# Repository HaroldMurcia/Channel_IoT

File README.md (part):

# Channel_IoT

# **Índice**   
- 1 [INSTALACION DE HERRAMIENTAS](#id1)
  - 1.1 [MPLABX](#id2)
  - 1.2 [Instalación de **MPLAB X** en Ubuntu](#id3)
  - 1.3 [Instalación del compilador XC8 en ubuntu ](#id4)
  - 1.4 [Instalación de MPLAB CODE CONFIGURATOR MCC ](#id5)
  - 1.5 [LoRa Development Suite](#id6)
- 2 [HARDWARE](#id7)
  - 2.1 [Documentos relacionados ](#id8) 
  - 2.2 [Requerimientos de hardware](#id9)
  - 2.3 [Enlaces de interés](#id10)
- 3 [Diseño de schematic y PCB en Eagle](#id11)
  - 3.1 [Estructura de la PCB](#id12)
  - 3.2 [PCB  Botton y Top](#id13)
  - 3.3 [Modelo PCB en 3D](#id14)
- 4 [Errores de diseño](#id36)
- 5 [Comandos modulo RN2903](#id15)
   - 5.1 [Comandos radio ](#id16)
     - 5.1.1 [Comandos para inicializar el radio **modulación LoRa**](#id17)
     - 5.1.2 [Comandos de transmisión](#id18)
     - 5.1.3 [Comandos de recepción](#id19) 
- 6 [Protocolo serial ](#id21)
  - 6.1 [Tablas de contenido del mensaje](#id22)
    - 5.1.1 [Cabecera del mensaje](#id23)
    - 5.1.2 [Tabla de familia](#id24)
    - 5.1.2 [Descripción tablas](#id25)
- 7 [Documentación de código](#id26)
-  6.1 [Versiones de software](#id27)
    - 7.1.1 [Programación en PIC18Lf45k50](#id28)
    - 7.1.2 [Programación en dsPIC30F4011](#id29)
    - 7.1.2 [Interfaz nodo maestro](#id30)
- 8 [Resultados](#id31)
  - 8.1 [Apertura de compuerta](#id32)
  - 8.2 [Distancia del sensor de ultrasonido](#id33)
  - 8.3 [Alimentación de la board](#id34)
  - 8.4 [Temperatura de la board](#id35)

# INSTALACION DE HERRAMIENTAS  
## MPLABX  
Este algoritmo se ha realizado en [Mplab x IDE](https://www.microchip.com/en-us/development-tools-tools-and-software/mplab-x-ide) Versión 5.50 en el compilador [XC8]( https://www.microchip.com/en-us/development-tools-tools-and-software/mplab-xc-compilers) versión 2.32. A su vez se usó el plugin MCC [MPLAB® Code Configurator]( https://www.microchip.com/en-us/development-tools-tools-and-software/embedded-software-center/mplab-code-configurator) el cual esta disponible para windows linux y mac, este ayuda a generar las librerías básicas del micro controlador, cabe aclarar que la familia dspic30 no tiene soporte en este plugin.

## Instalación de **MPLAB X** en Ubuntu  
Primero se verifica la arquitectura de sistema, para ello abrimos una terminal y ejecutamos el siguiente comando:
```
uname - m
```

Se mira si la distribución de Linux tiene soporté de multi arquitectura en el caso de no tenerlo se debe instalar una librería especial
```
dpkg --print-foreign-architectures
```

Entonces aquí se observa que nos devuelve i386 lo que quiere decir que, si es multi arquitectura, ahora antes de seguir con el proceso se debe verificar que no haya actualizaciones del sistema 
```
sudo apt-get update
```
Ahora lo que se debe hacer es instalar las librerías para que **MPLAB**  sea compatible con instrucciones de procesador de 32bits
```
sudo apt-get install libc6:i386 libx11-6:i386 libxext6:i386 libstdc++6:i386 libexpat1:i386
```

Ahora se busca la  página oficial de microchip para descargar [MPLAB X IDE]( https://www.microchip.com/en-us/development-tools-tools-and-software/mplab-x-ide) en la sección de **Downloads, Documentation and Other Resources**
Después de haber descargado el software, nos dirigimos a la carpeta en la que se descargo
```
cd descargas/
```
Para la instalación del software, se descomprime el archivo y se convierte el archivo descargado a ejecutable  
```
tar -xvf MPLABX-v5.50-linux-installer.tar
chmod u+x MPLABX-v5.50-linux-installer.sh
```

Ejecutar el instalador 
```
sudo ./MPLABX-v5.50-linux-installer.sh
```

A continuación, se muestra las partes mas importantes del instalador 

Al final de la instalación se debe reiniciar el PC para completar el proceso de instalación 

## Instalación del compilador XC8 en ubuntu  
Ahora es necesario instalar el compilador para el microcontrolador que desee trabajar 8bits,16bits y 32bits [MPLAB XC]( https://www.microchip.com/en-us/development-tools-tools-and-software/mplab-xc-compilers) sección **Downloads, Documentation and Other Resources** y **compiler dowloads**

Después de haber descargado la aplicación, vamos a la carpeta en la que lo guardamos y lo volvemos un ejecutable y lo ejecutamos 
```
chmod u+x xc8-v2.32-full-install-linux-x64-installer.run
sudo ./xc8-v2.32-full-install-linux-x64-installer.run
```

Se deja todo por defecto y next

Al final de la instalación se debe reiniciar el PC para completar el proceso de instalación

## Instalación de MPLAB CODE CONFIGURATOR MCC  
Cabe aclarar que MCC es solamente compatible con la ultima versión de MPLAB X y esta disponible para todos los sistemas operativos. Además el procesos se realizo en ubuntu, sin embargo es el mismo proceso para Windows y MAC os.

MCC es un plugin que permite configurar algunos microcontroladores de una manera rápida y sencilla, ya que este genera una interfaz en la que se puede configurar una serie de parámetros, utilizar algunas librerías y este genera código de la librería según los parámetros estipulados  para comenzar a trabajar en el proyecto.

**Nota: MCC no es compatible con la familia DSPIC30**

* Abrir la aplicación de MPLAB X IDE
* Tools
* plugins
* Available Plugins
* Y buscamos MPLAB Code Configurator 
* Pulsar en install

Al final de la instalación se escoge reset now, y se reinicia MPLAB X después aparecerá de la siguiente manera, “si no se ha creado ningún proyecto”

## LoRa Development Suite  

Es una interfaz grafica que permite la configuración de los diferentes comandos que implementa modulo RN2903 y RN2483, de esta manera el usuario aprenda como debe enviar los datos de manera serial sin muchas complicaciones, **cabe aclarar que esta interfaz no es estrictamente necesaria para configurar el módulo RN2903,ya que es una guía, de igual forma, los comandos se pueden enviar mediarte el UART programndo el  microcontrolador** para más información  mirar la guía de comandos del [módulo RN2903]( https://ww1.microchip.com/downloads/en/DeviceDoc/RN2903%20LoRa%20Technology%20Module%20Command%20Reference%20User%20Guide-40001811B.pdf)

### instalación
Esta aplicación esta disponible para todos los sistemas operativos y se puede encontrar en la [pagina oficial de microchip]( https://www.microchip.com/wwwproducts/en/RN2903), en el apartado de **Documents**, **software libreires/firmware** se encuentran las aplicaciones, solo basta con abrir la aplicación darle next y **mirar la ruta de la carpeta en la que se va instalar ya que se debe ir a buscar la ampliación a ese  directorio** esto es para el caso de Windows. Ir al siguiente enlace en caso de [Linux
]( https://www.gaggl.com/2018/04/microchip-lorawan-development-utility-on-ubuntu/)

### RN2903 ACTUALIZAR FIREWARE
El siguiente video tiene como objetivo explicar la forma de actualizar el firmware del modulo RN2903 de la tarjeta LoRa Mote, dado el caso de que se allá borrado el firmware del módulo RN2903 [Video en youtube](https://youtu.be/kyjtmIkalMk)

# HARDWARE  
Este repositorio tiene como objetivo mostrar  los elementos que componen el sistema y su configuración en con construcción de esta, es decir la asignación de pines o conexiones de los dispositivos entre si.

## Documentos relacionados  
* [Configuración o asignación de pines](https://docs.google.com/spreadsheets/d/19cve4B_YzyOGqIv9DEK3eCqArvopMfsAZXm61Hay0jQ/edit?usp=sharing)

* [Google Drive](https://drive.google.com/drive/folders/19VFRMTp_xo8fuAuP7UYOIrlyNO1dNOWd?usp=sharing)
* [Diagrama de bloques](https://drive.google.com/file/d/1_osPgyQmuKj5nIkt5gdU3hPU3BZLeOLT/view?usp=sharing)
* [Schematic](https://github.com/HaroldMurcia/Channel_IoT/blob/master/Eagle/schematic.pdf)

## Requerimientos de hardware  
A continuación se muestran los componentes principales que encabezan el sistema, los demás dispositivos se encuentran en [Datasheet]( https://github.com/HaroldMurcia/Channel_IoT/tree/master/Hardware/Datasheet)
* [MaxSonar](https://co.mouser.com/ProductDetail/DFRobot/SEN0272?qs=T8HDo%252BTk69VWj8BEbH%252BU3Q%3D%3D)
* [LoRa Mote](https://www.microchip.com/Developmenttools/ProductDetails/dm164139)
* [Microchip RN2903](https://www.microchip.com/wwwproducts/en/RN2903)
* [Dspic30f4011](https://www.microchip.com/wwwproducts/en/dsPIC30F4011)

## Enlaces de interés  
* [Platformio](https://platformio.org/)
* [RAdioHead](https://www.airspayce.com/mikem/arduino/RadioHead/)

# Diseño de schematic y PCB en Eagle  
[Cotización de los componentes](https://docs.google.com/spreadsheets/d/1AnpxCE8uhZ4Mzhw6TfTGnhGRriO4N8LUufEemXK9A1I/edit#gid=807096094) En este link se entra la cotización de los diferentes componentes usados en la PCB exceptuando la tarjeta LoRa mote, Dspic, Tblocks y buzzer, dicha cotización se realizo para armar 3 tarjetas, mas adelante se describe  de manera superficial la función del componente.

## Estructura de la  PCB  
En el siguiente [enlace](https://docs.google.com/spreadsheets/d/1AnpxCE8uhZ4Mzhw6TfTGnhGRriO4N8LUufEemXK9A1I/edit#gid=1786186541) se encontrarán la distribución de los pines del DSpic para realizar las diferentes conexiones, este archivo contiene el número del pin, así como el label del esquemático de Eagle su tipo de puerto, es decir si es ADC, Digital etc.

La siguiente imagen muestra la distribución de cada uno de los componentes usados para la Pcb, estos componentes tienen su letra y numero correspondiente o identificador del componente, además de su valor si este lo requiere, cada  uno de los componentes se situó de manera estratégica, de tal manera que sea fácil soldar y acceder a este; de igual forma cada elemento esta lo más cerca posible a la conexión con otros dispositivos con los que se interconecta con el fin de tener la menor resistencia posible en la pista que los interconecta. 
La siguiente [tabla](https://docs.google.com/spreadsheets/d/1AnpxCE8uhZ4Mzhw6TfTGnhGRriO4N8LUufEemXK9A1I/edit#gid=1117524344) muestra la descripción mas detallada de cada elemento de la PCB.

Como se puede evidenciar la pcb diseñada es doble capa y cuenta con dos tamaños de anchura, cada uno de estos tamaños fueron calculados por medio de la norma IPS2221, estos cálculos se hicieron por medio de una calculadora que ofrece [Digikey]( https://www.digikey.com/es/resources/conversion-calculators/conversion-calculator-pcb-trace-width) para ello se busco en el datasheet de cada unos de los componentes las corrientes nominales, el consumo de cada uno de los componentes es bajo y en ancho de la pista es muy pequeño, por tanto por requerimientos mínimos que exigen algunas empresas para la fabricación de las pcb para  cada pista debe ser de 0.2mm, para este diseño se tomo un valor por arriba que es de 0.254mm, por otra parte para el calculo de las pistas de potencia se sumo la corriente nominal de todos los componentes, esto se hizo buscado el peor de los casos, lo cual hace suponer que todos los componentes están encendidos en el mismo momento. La corriente total fue alrededor de 1.3A, por tanto el anchor de la pista es de 0.55mm, sin embargo se sobre dimensiono un poco ya que algunos dispositivos pueden tener picos de corriente que muchas veces  no se especifica en el datasheet por tanto el ancho es de 1.016mm, por ultimo para realizar el cálculo se escogió una temperatura ambiente de 25°C y el aumento de temperatura de 30°C el espesor de 1oz/ft^2. 
[Tabla de cosumo y calculos de ruteo](https://docs.google.com/spreadsheets/d/1AnpxCE8uhZ4Mzhw6TfTGnhGRriO4N8LUufEemXK9A1I/edit#gid=618312286)

## PCB  Caras Botton Y Top  

## Modelo PCB en 3D 
La Pcb cuenta con diferentes componentes, la alimentación cuenta con un conector molex de 4 pines, el cual tiene una sola forma de conectar, por otra parte los indicadores visuales y audibles son indicadores del estado en que se encuentran el sistema, por otra parte el microcontrolador es que se encargara de procesar los diferentes sensores, procesamiento de datos y envió de datos al LoRa, por otra parte los sensores se leen mediante ADC, el bloque de comunicación de sistema de potencia se usa para comunicar un sistema de potencia que se encarga de abrir o cerrar la compuerta, los botones de calibración sirven para abrir o cerrar la compuerta calibrar la altura de sensores sonar, por último se dejó un puerto para programar el microcontrolador con un pickit mediante ICSP.

[Modelo en fusion360](https://a360.co/3zkWzcB)
Clave: 159753

# Errores de diseño 
- El primer error se encuentra en la parte de los pulsadores, las pistas para soldar cada pulsador son muy cortas, por tanto se deben dejar con mayor longitud a la actual, con el fin de que el pulsador se pueda soldar con mayor facilidad.
- cuando se construyeron las librerías del ADC, en la hoja de datos de la familia dsPIC30f se especifica que se deben conectar los pines 40 y 39 a la alimentación para la referencia del ADC, no obstante, la hoja de datos del dsPIC30f4011 especificaba que los pines eran usados para colocar un voltaje entre 2.7 y 5V, con lo anterior, se colocaron dos cables entre la base del dsPIC y el MCU, para poder leer las señales análogicas provenientes de los sensores.

# Comandos modulo RN2903

El modulo RN2903 tiene una gran cantidad de comandos, sin embargo solo se deben usar una cabecera para la comunicación ya sea **mac o radio**, en esta sección se implementaron los comandos radio, estos facilitan la comunicación entre dos módulos RN2903.

Por otra parte, los comandos en general se deben enviar con la misma cantidad de espacios que especifica la hoja de datos, a su vez al final de cada comando se de enviar retorno de carro **CR** y salto de línea **LF** .

## Comandos radio

### Comandos para inicializar el radio **modulación LoRa**

1. El siguiente comando permite cambiar el método de modulación utilizado por el módulo.
Además, la modificación del modo de funcionamiento no afecta los parámetros, variables o
registros previamente configurados. Así mismo, el comando es muy simple ya que solamente
decide si es LoRa o FSK. En este documento se trabaja los comandos relacionados con LoRa.
```http
  radio set mod <mode>
```
| Parametro   | Comando  | Parametro     |Description parametro              | Tipo de respuesta    |
| :--------   | :------- | :------------ |:--------------------------------- | :--------------------|
| `radio set` |  `mod`   | `<mode>`      |**String**. lora o fsk             |  ok o invalid_param  |

`Ejemplo` 
```http
  radio set mod lora\r\n
```
2. El siguiente comando determina la potencia de salida del transceptor. La cual se puede
ajustar por encima del límite especificado, este ajuste de potencia permite compensar algunas
pérdidas en el cable o línea de transmisión en dBm. El valor máximo que puede alcanzar es
de 17 dBm a 20 dBm
```http
  radio set pwr <pwrOut>
```
| Parametro   | Comando  |   Parametro   |Description parametro              | Tipo de respuesta    |
| :--------   | :------- | :------------ |:--------------------------------- | :--------------------|
| `radio set` |  `pwr`   |   `<pwrOut>`  |**Decimal**. de 2 hasta 20         |  ok o invalid_param  |

`Ejemplo` 
```http
   radio set pwr 3\r\n 
```
3. Este comando establece el ancho de banda de radio para el funcionamiento de LoRa,
ambos dispositivos deben tener el mismo ancho de banda, puesto que, ambos dispositivos se
comportan como transmisor y receptor 
```http
  radio set bw <bandWidth>
```
| Parametro   | Comando  |   Parametro   |Description parametro              | Tipo de respuesta    |
| :--------   | :------- | :------------ |:--------------------------------- | :--------------------|
| `radio set` |  `bw`   |   `<bandWidth>`  |**Decimal**. puede ser de 125,250,500 en KHz         |  ok o invalid_param  |

`Ejemplo` 
```http
   radio set bw 250\r\n 
```
4. El comando crc permite activar o desactivar la detección de errores, CRC Cyclic Redun-
dancy Check este comando se usa para detectar errores o cambios accidentales en datos
sin procesar. Por tanto, si el detector de errores encuentra irregularidades en los mensajes
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
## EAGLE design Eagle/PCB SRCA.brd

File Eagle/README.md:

# **Índice**   
- 3 [Diseño de schematic y PCB en Eagle](#id11)
  - 3.1 [ESTRUCTURA DEL PCB](#id12)
  - 3.2 [PCB TERMINADA CARAS BUTTOM Y TOP](#id13)
  - 3.3 [MODELO PCB EN 3D](#id14)

# Diseño de schematic y PCB en Eagle  
[Cotización de los componentes](https://docs.google.com/spreadsheets/d/1AnpxCE8uhZ4Mzhw6TfTGnhGRriO4N8LUufEemXK9A1I/edit#gid=807096094) En este link se entra la cotización de los diferentes componentes usados en la PCB exceptuando la tarjeta LoRa mote, Dspic, Tblocks y buzzer, dicha cotización se realizo para armar 3 tarjetas, mas adelante se describe  de manera superficial la función del componente.
## ESTRUCTURA DEL PCB  
En el siguiente [enlace](https://docs.google.com/spreadsheets/d/1AnpxCE8uhZ4Mzhw6TfTGnhGRriO4N8LUufEemXK9A1I/edit#gid=1786186541) se encontrarán la distribución de los pines del DSpic para realizar las diferentes conexiones, este archivo contiene el número del pin, así como el label del esquemático de Eagle su tipo de puerto, es decir si es ADC, Digital etc.

La siguiente imagen muestra la distribución de cada uno de los componentes usados para la Pcb, estos componentes tienen su letra y numero correspondiente o identificador del componente, además de su valor si este lo requiere, cada  uno de los componentes se situó de manera estratégica, de tal manera que sea fácil soldar y acceder a este; de igual forma cada elemento esta lo más cerca posible a la conexión con otros dispositivos con los que se interconecta con el fin de tener la menor resistencia posible en la pista que los interconecta. 
La siguiente [tabla](https://docs.google.com/spreadsheets/d/1AnpxCE8uhZ4Mzhw6TfTGnhGRriO4N8LUufEemXK9A1I/edit#gid=1117524344) muestra la descripción mas detallada de cada elemento de la Pcb.

Como se puede evidenciar la pcb diseñada es doble capa y cuenta con dos tamaños de anchura, cada uno de estos tamaños fueron calculados por medio de la norma IPS2221, estos cálculos se hicieron por medio de una calculadora que ofrece [Digikey]( https://www.digikey.com/es/resources/conversion-calculators/conversion-calculator-pcb-trace-width) para ello se busco en el datasheet de cada unos de los componentes las corrientes nominales, el consumo de cada uno de los componentes es bajo y en ancho de la pista es muy pequeño, por tanto por requerimientos mínimos que exigen algunas empresas para la fabricación de las pcb para  cada pista debe ser de 0.2mm, para este diseño se tomo un valor por arriba que es de 0.254mm, por otra parte para el calculo de las pistas de potencia se sumo la corriente nominal de todos los componentes, esto se hizo buscado el peor de los casos, lo cual hace suponer que todos los componentes están encendidos en el mismo momento. La corriente total fue alrededor de 1.3A, por tanto el anchor de la pista es de 0.55mm, sin embargo se sobre dimensiono un poco ya que algunos dispositivos pueden tener picos de corriente que muchas veces  no se especifica en el datasheet por tanto el ancho es de 1.016mm, por ultimo para realizar el cálculo se escogió una temperatura ambiente de 25°C y el aumento de temperatura de 30°C el espesor de 1oz/ft^2. 
[Tabla de cosumo y calculos de ruteo](https://docs.google.com/spreadsheets/d/1AnpxCE8uhZ4Mzhw6TfTGnhGRriO4N8LUufEemXK9A1I/edit#gid=618312286)

## PCB TERMINADA CARAS BUTTOM Y TOP  

## MODELO PCB EN 3D 
La Pcb cuenta con diferentes componentes, la alimentación cuenta con un conector molex de 4 pines, el cual tiene una sola forma de conectar, por otra parte los indicadores visuales y audibles son indicadores del estado en que se encuentran el sistema, por otra parte el microcontrolador es que se encargara de procesar los diferentes sensores, procesamiento de datos y envió de datos al LoRa, por otra parte los sensores se leen mediante ADC, el bloque de comunicación de sistema de potencia se usa para comunicar un sistema de potencia que se encarga de abrir o cerrar la compuerta, los botones de calibración sirven para abrir o cerrar la compuerta calibrar la altura de sensores sonar, por último se dejó un puerto para programar el microcontrolador con un pickit mediante ICSP.

[Modelo en fusion360](https://a360.co/3zkWzcB)
Clave: 159753

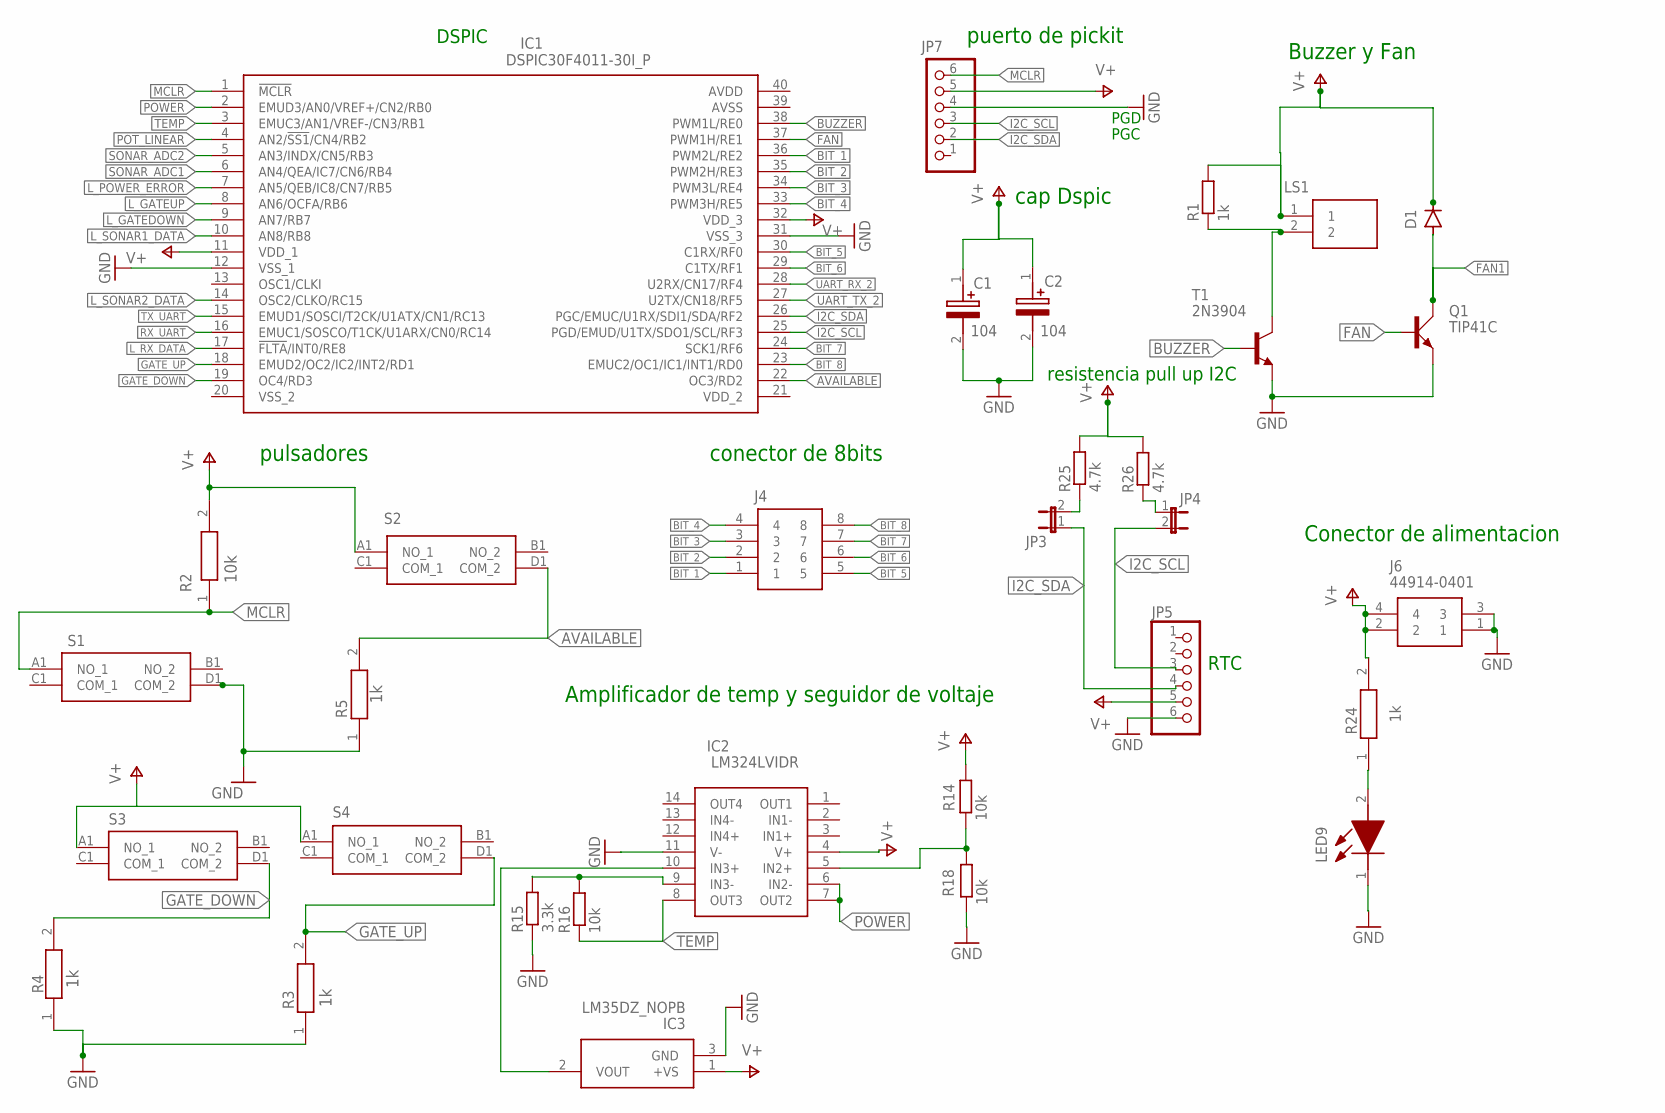
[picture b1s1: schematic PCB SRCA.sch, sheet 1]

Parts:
C1, C2: TAJR104K020RNJ; CAPPM2014X120N
D1: 1N4148DO35-7; DO35-7
IC1: DSPIC30F4011-30I_P; DIP1543W58P254L5175H635Q40N
IC2: LM324LVIDR; SOIC127P600X175-14N
IC3: LM35DZ_NOPB; LP0003A
J4: 44914-0801
J6: 44914-0401
JP3, JP4: JP1E; JP1
JP5, JP7: PINHD-1X6; 1X06
LED9: 599-0181-007F; LEDC2012X70N
LS1: PS1240P02BT
Q1: TIP41C; TO220AV
R1: 1k; 0207/10
R2, R3, R4, R5, R24: RC0805FR-071KL; RESC2012X60N
R14, R16, R18: 10k; 0207/10
R15: 3.3k; 0207/10
R25, R26: 4.7k; 0207/10
S1, S2, S3, S4: PTS645SK50JSMTR92_LFS; PTS645SK50JSMTR92LFS
T1: 2N3904; TO92

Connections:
AVAILABLE: IC1.22 (OC3/RD2), R5.2, S2.D1 (COM_2)
BIT_1: IC1.36 (PWM2L/RE2), J4.1
BIT_2: IC1.35 (PWM2H/RE3), J4.2
BIT_3: IC1.34 (PWM3L/RE4), J4.3
BIT_4: IC1.33 (PWM3H/RE5), J4.4
BIT_5: IC1.30 (C1RX/RF0), J4.5
BIT_6: IC1.29 (C1TX/RF1), J4.6
BIT_7: IC1.24 (SCK1/RF6), J4.7
BIT_8: IC1.23 (EMUC2/OC1/IC1/INT1/RD0), J4.8
BUZZER: IC1.38 (PWM1L/RE0), T1.2 (B)
FAN: IC1.37 (PWM1H/RE1), Q1.B
FAN1: D1.A, Q1.C; also elsewhere on the board
GATE_DOWN: IC1.19 (OC4/RD3), R4.2, S3.D1 (COM_2)
GATE_UP: IC1.18 (EMUD2/OC2/IC2/INT2/RD1), R3.2, S4.D1 (COM_2)
GND: C1.2 (-), C2.2 (-), IC1.12 (VSS_1), IC1.31 (VSS_3), IC2.11 (V-), IC3.3 (GND), J6.1, J6.3, JP5.6, JP7.4, LED9.1 (K), Q1.E, R3.1, R4.1, R5.1, R15.1, R18.1, S1.D1 (COM_2), T1.3 (E); also elsewhere on the board
I2C_SCL: IC1.25 (PGD/EMUD/U1TX/SDO1/SCL/RF3), JP4.2, JP5.3, JP7.3; also elsewhere on the board
I2C_SDA: IC1.26 (PGC/EMUC/U1RX/SDI1/SDA/RF2), JP3.1, JP5.4, JP7.2; also elsewhere on the board
L_GATEDOWN: IC1.9 (AN7/RB7); also elsewhere on the board
L_GATEUP: IC1.8 (AN6/OCFA/RB6); also elsewhere on the board
L_POWER_ERROR: IC1.7 (AN5/QEB/IC8/CN7/RB5); also elsewhere on the board
L_RX_DATA: IC1.17 (!FLTA!/INT0/RE8); also elsewhere on the board
L_SONAR1_DATA: IC1.10 (AN8/RB8); also elsewhere on the board
L_SONAR2_DATA: IC1.14 (OSC2/CLKO/RC15); also elsewhere on the board
MCLR: IC1.1 (!MCLR), JP7.6, R2.1, S1.A1 (NO_1)
unnamed: IC2.9 (IN3-), R15.2, R16.2
unnamed: IC2.10 (IN3+), IC3.2 (VOUT)
unnamed: JP3.2, R25.1
unnamed: LS1.2, R1.1, T1.1 (C)
unnamed: LED9.2 (A), R24.1
unnamed: JP4.1, R26.1
unnamed: IC2.5 (IN2+), R14.1, R18.2
POT_LINEAR: IC1.4 (AN2/!SS1!/CN4/RB2); also elsewhere on the board
POWER: IC1.2 (EMUD3/AN0/VREF+/CN2/RB0), IC2.6 (IN2-), IC2.7 (OUT2)
RX_UART: IC1.16 (EMUC1/SOSCO/T1CK/U1ARX/CN0/RC14); also elsewhere on the board
SONAR_ADC1: IC1.6 (AN4/QEA/IC7/CN6/RB4); also elsewhere on the board
SONAR_ADC2: IC1.5 (AN3/INDX/CN5/RB3); also elsewhere on the board
TEMP: IC1.3 (EMUC3/AN1/VREF-/CN3/RB1), IC2.8 (OUT3), R16.1
TX_UART: IC1.15 (EMUD1/SOSCI/T2CK/U1ATX/CN1/RC13); also elsewhere on the board
UART_RX_2: IC1.28 (U2RX/CN17/RF4); also elsewhere on the board
UART_TX_2: IC1.27 (U2TX/CN18/RF5); also elsewhere on the board
V+: C1.1 (+), C2.1 (+), D1.C, IC1.11 (VDD_1), IC1.32 (VDD_3), IC2.4 (V+), IC3.1 (+VS), J6.2, J6.4, JP5.5, JP7.5, LS1.1, R1.2, R2.2, R14.2, R24.2, R25.2, R26.2, S2.A1 (NO_1), S3.A1 (NO_1), S4.A1 (NO_1); also elsewhere on the board

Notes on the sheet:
pulsadores
Amplificador de temp y seguidor de voltaje
conector de 8bits
cap Dspic
puerto de pickit
Conector de alimentacion
resistencia pull up I2C
RTC
DSPIC
10k
104
Buzzer y Fan
PGD
PGC

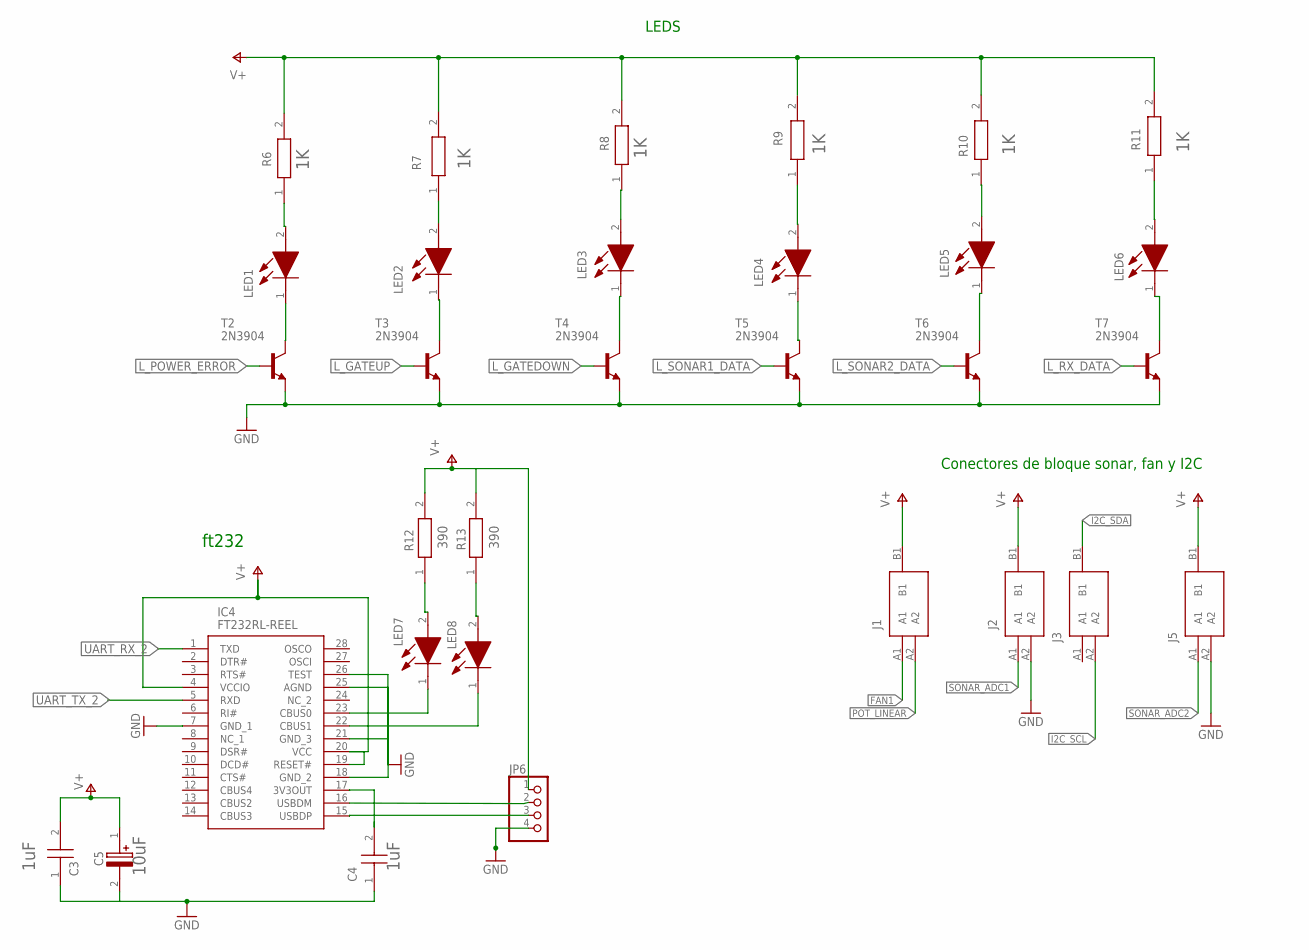
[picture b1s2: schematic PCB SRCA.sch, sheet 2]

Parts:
C3, C4: C0805X104K1RAC3316; CAPC2012X100N
C5: UUP1C100MCL1GS; CAPAE530X610N
IC4: FT232RL-REEL; SOP65P778X200-28N
J1, J2, J3, J5: TBL002A-350-03GR-2OR; TBL002A35003GR2OR
JP6: PINHD-1X4; 1X04
LED1, LED2, LED3, LED4, LED5, LED6, LED7, LED8: 599-0181-007F; LEDC2012X70N
R6, R7, R8, R9, R10, R11, R12, R13: RC0805FR-071KL; RESC2012X60N
T2, T3, T4, T5, T6, T7: 2N3904; TO92

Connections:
FAN1: J1.A1; also elsewhere on the board
GND: C3.1, C4.1, C5.2 (-), IC4.7 (GND_1), IC4.18 (GND_2), IC4.21 (GND_3), IC4.25 (AGND), IC4.26 (TEST), J2.A2, J5.A2, JP6.4, T2.3 (E), T3.3 (E), T4.3 (E), T5.3 (E), T6.3 (E), T7.3 (E); also elsewhere on the board
I2C_SCL: J3.A2; also elsewhere on the board
I2C_SDA: J3.B1; also elsewhere on the board
L_GATEDOWN: T4.2 (B); also elsewhere on the board
L_GATEUP: T3.2 (B); also elsewhere on the board
L_POWER_ERROR: T2.2 (B); also elsewhere on the board
L_RX_DATA: T7.2 (B); also elsewhere on the board
L_SONAR1_DATA: T5.2 (B); also elsewhere on the board
L_SONAR2_DATA: T6.2 (B); also elsewhere on the board
unnamed: LED1.2 (A), R6.1
unnamed: IC4.23 (CBUS0), LED7.1 (K)
unnamed: LED1.1 (K), T2.1 (C)
unnamed: LED2.2 (A), R7.1
unnamed: LED2.1 (K), T3.1 (C)
unnamed: LED3.1 (K), T4.1 (C)
unnamed: LED4.2 (A), R9.1
unnamed: LED5.2 (A), R10.1
unnamed: LED3.2 (A), R8.1
unnamed: LED4.1 (K), T5.1 (C)
unnamed: LED6.2 (A), R11.1
unnamed: LED7.2 (A), R12.1
unnamed: LED8.2 (A), R13.1
unnamed: LED5.1 (K), T6.1 (C)
unnamed: LED6.1 (K), T7.1 (C)
unnamed: IC4.22 (CBUS1), LED8.1 (K)
unnamed: C4.2, IC4.17 (3V3OUT)
unnamed: IC4.16 (USBDM), JP6.2
unnamed: IC4.15 (USBDP), JP6.3
POT_LINEAR: J1.A2; also elsewhere on the board
SONAR_ADC1: J2.A1; also elsewhere on the board
SONAR_ADC2: J5.A1; also elsewhere on the board
UART_RX_2: IC4.1 (TXD); also elsewhere on the board
UART_TX_2: IC4.5 (RXD); also elsewhere on the board
V+: C3.2, C5.1 (+), IC4.4 (VCCIO), IC4.19 (RESET#), IC4.20 (VCC), J1.B1, J2.B1, J5.B1, JP6.1, R6.2, R7.2, R8.2, R9.2, R10.2, R11.2, R12.2, R13.2; also elsewhere on the board

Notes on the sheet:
Conectores de bloque sonar, fan y I2C
LEDS
390
ft232
1uF
10uF

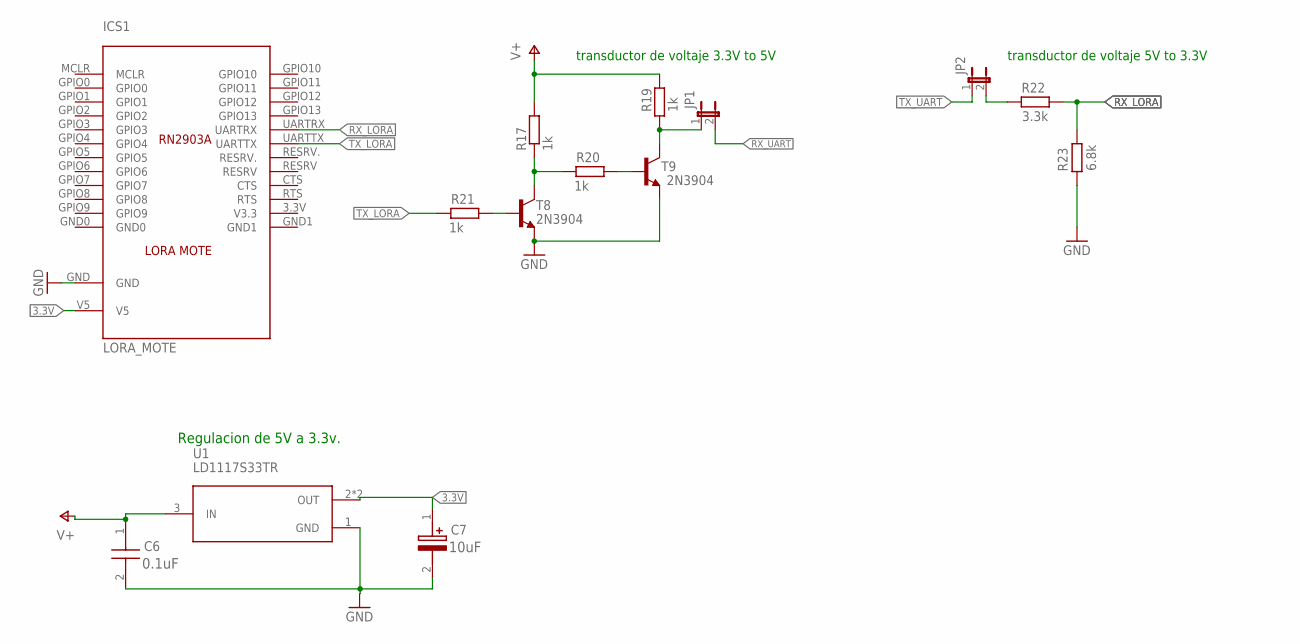
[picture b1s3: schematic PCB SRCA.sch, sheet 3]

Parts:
C6: C0805X104K1RAC3316; CAPC2012X100N
C7: UUP1C100MCL1GS; CAPAE530X610N
ICS1: LORA_MOTE; LORA_MOTE_RN2903
JP1, JP2: JP1E; JP1
R17, R19, R20, R21: 1k; 0207/10
R22: 3.3k; 0207/10
R23: 6.8k; 0207/10
T8, T9: 2N3904; TO92
U1: LD1117S33TR; SOT230P700X180-4N

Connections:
3.3V: C7.1 (+), ICS1.V5, U1.2 (OUT), U1.4 (OUT)
GND: C6.2, C7.2 (-), ICS1.GND, R23.2, T8.3 (E), T9.3 (E), U1.1 (GND); also elsewhere on the board
unnamed: R17.1, R20.2, T8.1 (C)
unnamed: R21.1, T8.2 (B)
unnamed: R20.1, T9.2 (B)
unnamed: JP2.2, R22.2
unnamed: JP1.1, R19.1, T9.1 (C)
RX_LORA: ICS1.UARTRX, R22.1, R23.1
RX_UART: JP1.2; also elsewhere on the board
TX_LORA: ICS1.UARTTX, R21.2
TX_UART: JP2.1; also elsewhere on the board
V+: C6.1, R17.2, R19.2, U1.3 (IN); also elsewhere on the board

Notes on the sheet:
transductor de voltaje 3.3V to 5V
transductor de voltaje 5V to 3.3V
Regulacion de 5V a 3.3v.
0.1uF
10uF

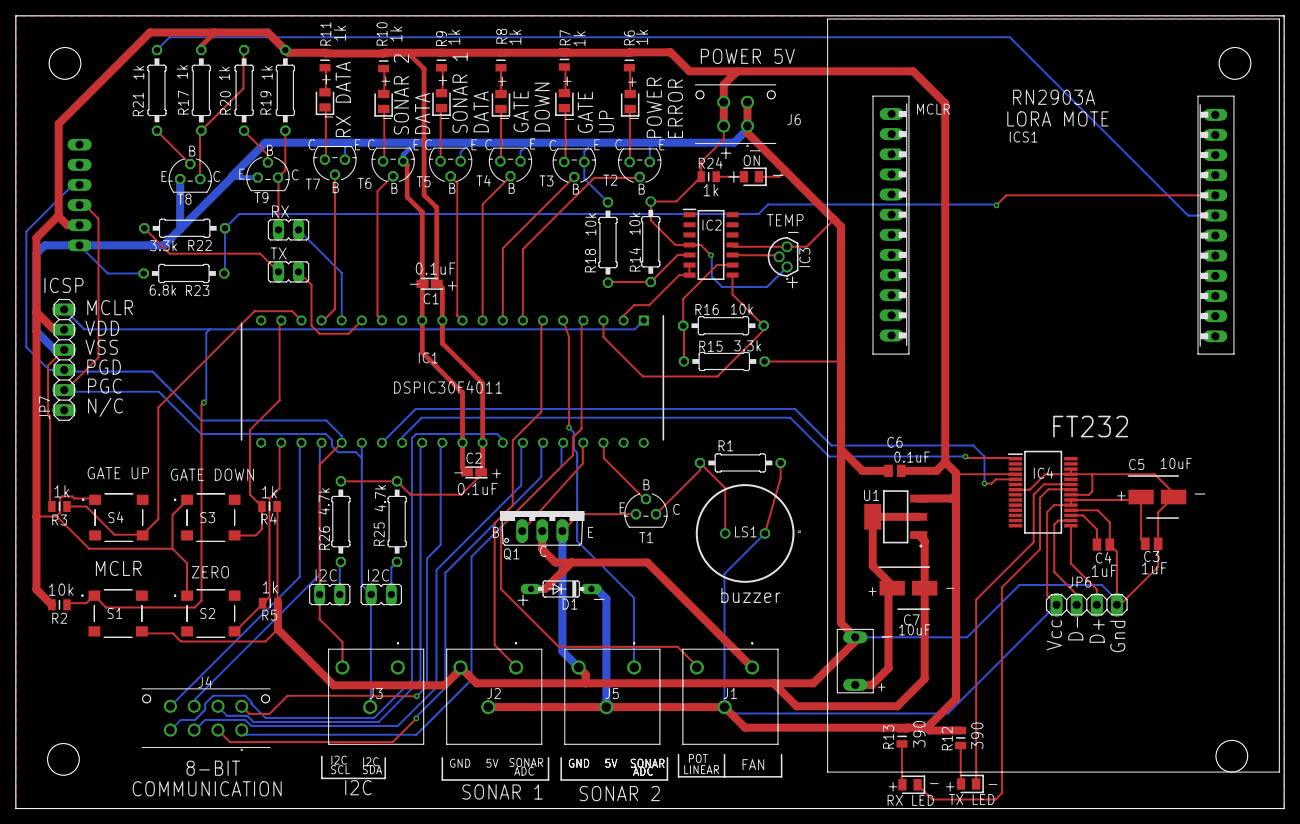
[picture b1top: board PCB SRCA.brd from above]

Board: 2 copper layers, 160.0 x 100.0 mm, 77 parts (1 on the bottom side), 68 nets.

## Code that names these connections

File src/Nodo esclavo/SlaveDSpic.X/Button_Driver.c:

/*
 * File  : Button_Driver.c
 * Author: Johan Avila 
 * Mail  : ingenieroavila21@gmail.com
 */

#include <xc.h>
#include "Button_Driver.h"

void Init_Button_Driver(void) {

    // init output Volts 0 
    LATDbits.LATD1 = 0;
    LATDbits.LATD2 = 0;
    LATDbits.LATD3 = 0;

    // determines id it is input(1) or output(0)
    TRISDbits.TRISD1 = 1; // RD1 Gate_Up
    TRISDbits.TRISD2 = 1; // RD2 Zero
    TRISDbits.TRISD3 = 1; // RD3 Gate_Down
}

// functions
// returns the value of the pin (1: 5 volts; 0: 0 volts)

int Button_Gate_Up(void) {
    return (PORTDbits.RD1);
}

int Button_Zero(void) {
    return (PORTDbits.RD2);
}

int Button_Gate_Down(void) {
    return (PORTDbits.RD3);
}

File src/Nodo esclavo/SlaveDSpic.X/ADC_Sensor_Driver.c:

/*
 * File:   Channel_Gate.c
 * Position : Estudiante de Paz y Region 
 * Author: Johan Avila 
 * Mail  : ingenieroavila21@gmail.com
 * Reviewer and approver  : Oscar Daniel Rodriguez Gallego
 * Change : Oscar Daniel Rodrguez Gallego
 */

#include <xc.h>

#include "ADC_Sensor_Driver.h"
#include "LoRa_RN2903A.h"

const float Resolution_ADC = (5.0) / (1024); // (AVDD / 2^10bit) 
// ok
float Volts_Power_ADC = 0.0; // RB0
float Volts_Temp_ADC = 0.0; // RB1
float Volts_Gate_ADC = 0.0; // RB2
float Volts_Sonar_2_ADC = 0.0; // RB3
float Volts_Sonar_1_ADC = 0.0; // RB4
float Voltaje_max=0.0,Voltaje_min=0.0;

void Init_ADC_Sensors_Driver(void) {
    // ADPCFG configuration ok
    TRISBbits.TRISB0 = 1;
    TRISBbits.TRISB1 = 1;
    TRISBbits.TRISB2 = 1;
    TRISBbits.TRISB3 = 1;
    TRISBbits.TRISB4 = 1;
    // digital ports 1 ; analog ports 0; ports B
    ADPCFGbits.PCFG0 = 0; // RB0 intput analog ports
    ADPCFGbits.PCFG1 = 0; // RB1 intput analog ports
    ADPCFGbits.PCFG2 = 0; // RB2 intput analog ports  
    ADPCFGbits.PCFG3 = 0; // RB3 intput analog ports
    ADPCFGbits.PCFG4 = 0; // RB4 intput analog ports
        // ADCON1 configuration ok
    ADCON1bits.ADSIDL = 0; // Continue module operation in Idle mode
    ADCON1bits.FORM = 0b00; // Data Output Format bits Integer
    ADCON1bits.SSRC = 0b000; // Clearing SAMP bit ends sampling and starts conversion
    ADCON1bits.SIMSAM = 0; // Samples multiple channels individually in sequence
    ADCON1bits.ASAM = 0; // A/D Sample Auto-Start bit,Sampling begins when SAMP bit set 

    // ADCON2 configuration ok
    ADCON2bits.VCFG = 0b000; // Voltage Reference(AVDD - AVSS)
    ADCON2bits.CSCNA = 0; // Do not scan inputs
    ADCON2bits.CHPS = 0b11; // Selects Channels Utilized CH0, CH1, CH2 and CH3
    ADCON2bits.BUFS = 1; //  A/D is currently filling buffer 0x8-0xF, user should access data in 0x0-0x7
    ADCON2bits.SMPI = 0b1000; // Sample/Convert Sequences Per Interrupt Selection bits
    ADCON2bits.BUFM = 1; // Buffer configured as two 8-word buffers ADCBUF(15...8), ADCBUF(7...0)
    ADCON2bits.ALTS = 1; // Uses MUX A input multiplexer settings for first sample, then alternate between MUX B and MUX A input multiplexer settings for all subsequent samples

    // ADCHS configuration ok
    // MUX A Multiplexer Setting bits
    ADCHSbits.CH123NA = 0b00; // CH1, CH2, CH3 negative input is VREF -
    ADCHSbits.CH123SA = 0; // CH1:AN0, CH2:AN1, CH3:AN2
    ADCHSbits.CH0NA = 0; // Channel 0 negative input is VREF-
    ADCHSbits.CH0SA = 0b0011; // CH0:AN3

    // MUX B Multiplexer Setting bits
    ADCHSbits.CH123NB = 0b00; // CH1, CH2, CH3 negative input is VREF -
    ADCHSbits.CH123SB = 0; // CH1:AN0, CH2:AN1, CH3:AN2
    ADCHSbits.CH0NB = 0; // Channel 0 negative input is VREF-
    ADCHSbits.CH0SB = 0b0100; // CH0:AN4

    // ADCSSL configuration add daniel rodriguez gallego
    ADCSSLbits.CSSL0 = 0;
    ADCSSLbits.CSSL1 = 0;
    ADCSSLbits.CSSL2 = 0;
    ADCSSLbits.CSSL3 = 0;
    ADCSSLbits.CSSL4 = 0;

    // ADCON3 configuration ok
    ADCON3bits.SAMC = 18; // Sample Time bits
    ADCON3bits.ADRC = 1; // A/D internal RC clock
    // TAD = 333.33 nsec
    // FCY = FOSC/4 120Mhz : 30Mhz
    // ADCS = ( (2*TAD) / (1/FCY) ) - 1
    ADCON3bits.ADCS = 9; // Conversion Clock Select bits
    
    ADCON1bits.ADON = 1; //  Conversion Status bit on
}

void Sensor_Reading_ADC(void) {

    ADCON1bits.SAMP = 1; // Bit para habilitar muestreo
    __delay_ms(10);
    ADCON1bits.SAMP = 0; // Retiene el muestreo

    // MUX A Multiplexer
    Volts_Power_ADC = (ADCBUF1 * Resolution_ADC ); // RB0
    Volts_Temp_ADC = (ADCBUF2 * Resolution_ADC * 100) / 4; // RB1 4 corresponde a la ganancia de AOP
    Volts_Gate_ADC = (ADCBUF3 * Resolution_ADC); // RB2  
    Volts_Sonar_2_ADC = (ADCBUF0 * 5); // RB3

    // MUX B Multiplexer
    Volts_Sonar_1_ADC = (ADCBUF4 * 5); // RB4
}

float Get_Volts_Power_ADC(void) {
    return Volts_Power_ADC;
}

float Get_Volts_Temp_ADC(void) {

    return Volts_Temp_ADC;
}

float Get_Percentage_Gate_ADC(void) {
    /*
     * como se tiene una condicion de un voltaje minimo y un voltaje maximo 
     * el porcentajes es una regla de 3, en la que la lectura del adc se le resta el voltaje minimo ya que este 
     * es un offeset, al igual se hace Voltaje maximo, la idea es que el voltaje minimo represente al cero
     * y el maximo al 100%
     */
    float percentage = ((Volts_Gate_ADC-Voltaje_min)*100)/(Voltaje_max - Voltaje_min);
    if(percentage<=0){
        percentage = 0;
    }else if(percentage >= 100)
    {
        percentage =100;
    }else{
        percentage = percentage;//el valor que tiene
    }
    return percentage;
}

float Get_Volts_Sonar_1_ADC(void) {
//    Led_Sonar1(1);
//    __delay_ms(50);
//    Led_Sonar1(0);
    return Volts_Sonar_1_ADC;
}

float Get_Volts_Sonar_2_ADC(void) {
//    Led_Sonar2(1);
//    __delay_ms(50);
//    Led_Sonar2(0);
    return Volts_Sonar_2_ADC;
}

void Init_Percentage(float Vmax, float Vmin){
    Voltaje_max = Vmax;
    Voltaje_min = Vmin; 
}

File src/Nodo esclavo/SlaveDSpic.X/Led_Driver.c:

/*
 * File  : Led_Driver.c
 * Position : Estudiante de Paz y Region 
 * Author: Johan Avila 
 * Mail  : ingenieroavila21@gmail.com
 * Reviewer and approver  : Oscar Daniel Rodriguez Gallego
 * Change : Oscar Daniel Rodrguez Gallego
 */

#include <xc.h>
//#include <libpic30.h>
#include "Led_Driver.h"


// 1 : On ; 0 : Off
void Init_Led_Driver(void)
{
    // digital ports 1 ; analog ports 0; ports B
    ADPCFGbits.PCFG5 = 1; // Rb5
    ADPCFGbits.PCFG6 = 1; // Rb6
    ADPCFGbits.PCFG7 = 1; // Rb7
    ADPCFGbits.PCFG8 = 1; // Rb8 

    // determines id it is input(1) or output(0)
    TRISBbits.TRISB5 = 0; // Reb     Rb5 Power Error
    TRISBbits.TRISB6 = 0; // Yellow  Rb6 Gateup 
    TRISBbits.TRISB7 = 0; // White   Rb7 GateDown
    TRISBbits.TRISB8 = 0; // Yellow  Rb8 Sonar1
    TRISCbits.TRISC15 = 0; // White   C15 Sonar2
    TRISEbits.TRISE8 = 0; // Yellow  E8  Rx

    // init output Volts 0 
    LATBbits.LATB5 = 0;
    LATBbits.LATB6 = 0;
    LATBbits.LATB7 = 0;
    LATBbits.LATB8 = 0;
    LATCbits.LATC15 = 0;
    LATEbits.LATE8 = 0;
}

// functions
// 1 : On ; 0 : Off

void Led_Power_Error(int option_LedDri) {
    LATBbits.LATB5 = option_LedDri;
}

void Led_Gateup(int option_LedDri) {
    LATBbits.LATB6 = option_LedDri;
}

void Led_GateDown(int option_LedDri) {
    LATBbits.LATB7 = option_LedDri;
}

void Led_Sonar1(int option_LedDri) {
    LATBbits.LATB8 = option_LedDri;
}

void Led_Sonar2(int option_LedDri) {
    LATCbits.LATC15 = option_LedDri;
}

void Led_Rx(int option_LedDri) {
    LATEbits.LATE8 = option_LedDri;
}
/// oscar daniel Rodriguez 
void Turn_on_pic(void)
{
    int i;
    int size = 2;
    for (i = 0; i < size; i++) 
    {
        LATBbits.LATB5 = ~LATBbits.LATB5;
        __delay_ms(50);
        LATBbits.LATB5 = ~LATBbits.LATB5;
        __delay_ms(50);
        LATBbits.LATB6 = ~LATBbits.LATB6;
        __delay_ms(50);
        LATBbits.LATB6 = ~LATBbits.LATB6;
        __delay_ms(50);
        LATBbits.LATB7 = ~LATBbits.LATB7;
        __delay_ms(50);
        LATBbits.LATB7 = ~LATBbits.LATB7;
        __delay_ms(50);
        LATBbits.LATB8 = ~LATBbits.LATB8;
        __delay_ms(50);
        LATBbits.LATB8 = ~LATBbits.LATB8;
        __delay_ms(50);
        LATCbits.LATC15 = ~LATCbits.LATC15;
        __delay_ms(50);
        LATCbits.LATC15 = ~LATCbits.LATC15;
        __delay_ms(50);
        LATEbits.LATE8 = ~LATEbits.LATE8;
        __delay_ms(50);
        LATEbits.LATE8 = ~LATEbits.LATE8;
        __delay_ms(50);
    }
}
void Led_turn_on_all(void){
        Led_Power_Error(1);
    Led_Gateup(1);
    Led_GateDown(1);
    Led_Sonar1(1);
    Led_Sonar2(1);
    Led_Rx(1);
    __delay_ms(300);

    //        LATBbits.LATB5 = 0;
    Led_Power_Error(0);
    Led_Gateup(0);
    Led_GateDown(0);
    Led_Sonar1(0);
    Led_Sonar2(0);
    Led_Rx(0);
    __delay_ms(300);
}

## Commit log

2021-03-24 24.03.2021
2021-04-01 datashet
    se agregaron los datasheet de el sensor ultra sonido, la tarjeta LoRa el Dspic.
2021-04-01 Diseño de PCB
2021-04-01 datasheet
2021-04-10 Correccion readme
    se agregaron los links de google drive, los link de la pagina oficial en la cual se compraron los componentes aun falta por especificar
    mas cosas
2021-04-14 schematic
    este documento contiene el desarrollos esquemático del pcb
2021-04-14 Update Readme.md
    Se arreglo el diagrama de bloques
2021-04-14 eagle
    esquematico con los pootprint
2021-04-14 esquematico
2021-04-15 pres macro
2021-04-21 actulizacion tarjeta
    se realiz ajustes del esquematico
2021-04-21 organizacion
2021-05-16 pdf tarjeta
    este pdf contiene el esquematico de las conexiones realizadas hasta el momento
2021-05-16 Esquematico
    se actulizo el esquematico
2021-05-16 16/05/2021
    actualizacion
2021-05-28 New links
2021-06-28 28/06/2021
    se agrego la documentación del código fuente de la tarjeta LoRa Mote
2021-06-28 28/06/2021
    Codigo fuente
2021-06-28 27/06/2021
2021-06-29 29/06/2021
    actualización del firmware de una tarjeta loRa
2021-07-06 6/07/2021
2021-07-07 6/07/2021
    actualizacion de codigos de transmision y recepcion
2021-07-07 06/07/2021
    cambio de carpeta
2021-07-07 06/07/2021
    explicación de lorasuit y comandos
2021-07-07 06/07/2021
2021-07-07 07/07/2021
2021-07-07 07/07/2021
    Se agrego el proceso de instalación de los programas usados aun falta agregar la instalacion de lora suit
2021-07-08 07/07/2021
    Se termino de agregar los coma nos de radio
2021-07-08 Harold 08.07.21 Tx>>Rx
2021-07-15 14/07/2021
    actualizacIón de la PCB
2021-07-21 21/07/2021
    cambios en las posiciones de los componentes y pistas
2021-07-22 22/07/2021
2021-07-22 22/07/2021
    Se actualizo la pcb con todos los componentes y pistas, además se agregó las librerías del proyecto
2021-08-12 11/08/2021
    cambios pre finales del pcb y sus componentes
2021-08-13 12/08/2021
    correccion de sensor de temperatura
2021-08-13 12/08/2021
2021-08-21 20/08/2021
    se adjunta los archivos de la PCB final con logo y archivo gerber
2021-08-23 23-08-2021
    actualizaciones de nombres y logos
2021-08-24 23-08-2021
    pcb y cotización
2021-08-24 24-08-2021
    correccion de errores en pistas
2021-08-25 25-08-2021
    Cotizacion colcircuiotso
2021-08-26 25-08-2021
    ajustes
2021-08-26 26-08-2021
    Actulizacion de la pcb correccion de pistas separacion entre ellas
2021-09-01 31-08-2021
    se agregaron las librerías del proyecto se hizo algunas correciones en la parte de el sensor de temperatura y se hizo se coloco un regulador de 5V a 3.3V para la lora mote
2021-09-01 31-08-2021
    imagenes del pcb
2021-09-01 31-08-2021
    se cargo las nuevas imágenes al readme y el modelo 3d
2021-09-01 01-09-2021
    readme para basar se en la construccion del protocolo
2021-09-05 04-09-2021
    cambios de la nueva pcb se agrego cambios del uart entre dspic y lora
2021-09-06 06-09-2021
    se revirtio el cambio de el divisor de voltaje del lora al DSPIC
2021-09-06 06/09/2021
2021-09-06 06-09-2021
2021-09-21 21-09-2021
2021-09-21 21-08-2021
    se adiciono la explicación del protocolo serial, aun falta agregar las funciones, se esta revisando un fallo especifico
2021-09-23 23-09-2021
2021-11-18 18-11-2021
    Copia de codigo de comunicacion avanzada de LoRa Mote a LoRa Mote
    1. aqui se encuentra la libreria Lora basica
    2. protocolo de comunicacion
2022-01-28 27/01/2022
2022-01-28 27-01-2022
2022-03-15 14-03-2022
    gif
2022-03-15 14-03-2022
    se agregó los datashet del proyecto
2022-03-15 14-03-2022
    pines
2022-03-16 15-03-2022
    dodigo del nodo eclavo
2022-03-24 24-03-2022
    Se agregó la interfaz grafica
2022-03-24 24-03-2022
2022-03-24 24-03-2022
    Se agrego los resultados
2022-03-25 25-03-2022
    actulización de veriones de librerias para los codigos
2022-04-06 06-04-2022
2022-04-06 -06-04-2022
2022-04-06 6-04-2022
